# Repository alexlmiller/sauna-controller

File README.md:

# Local & Smart Sauna Controller

Open-source sauna convenience control built around ESPHome and Home Assistant. Control your sauna from anywhere with no cloud dependencies or crappy apps and for 1/3rd the cost of the normal commercial units.

The project can be built two ways:

- **Build from components**: hand-wire off-the-shelf modules and DIN parts.
- **Build with the carrier PCB**: use the Rev B control board PCB for cleaner
  wiring and integrated low-voltage distribution.

Both current build paths use the same Rev B firmware and pin map. The optional
wall panel uses an Elecrow CrowPanel 2.1" rotary display over a short wired UART
link, with a WiFi/Home Assistant panel target available for desk testing.

## Safety

This project is for **convenience control only**. It is not a primary safety
system and must not replace the sauna heater's listed safety controls.

- Use only properly rated, UL/ETL/listed components where applicable.
- Use a heater that already has its required high-limit and safety systems.
- Have the enclosure, high-voltage wiring, grounding, overcurrent protection,
  conductor sizing, strain relief, and final installation reviewed and installed
  by a qualified electrician.
- Do not rely on ESPHome, Home Assistant, WiFi, the wall panel, or this PCB as
  life-safety equipment.

Read [`docs/SAFETY.md`](docs/SAFETY.md) before building.

## What It Controls

- Heater contactor with a 24 VDC coil
- Two DS18B20 temperature probes: ceiling and bench
- Door reed switch
- Manual-reset high-temp circuit in series with the contactor coil
- Relay feedback contact for welded/failed relay detection
- 24 V RGBW LED strip through four PWM MOSFET channels
- Optional wall panel over direct 3.3 V UART

## User Interface

The controller exposes its entities through Home Assistant and can also be used
from a phone dashboard or the optional wall panel.

### Home Assistant Device Page

### Phone Dashboard

## Build Paths

### Option 1: Build From Components

Use an ESP32 DevKitC, MOSFET driver modules, opto input modules, DIN power
supplies, fusing/protection, and terminal blocks. This is best for prototyping
or a one-off hand-wired build.

Start here: [`docs/BUILD-FROM-COMPONENTS.md`](docs/BUILD-FROM-COMPONENTS.md)

### Option 2: Build With the Carrier PCB

Use the Rev B control board carrier PCB. This is the preferred path for new
installs because it reduces point-to-point wiring and integrates the ESP32
carrier, output drivers, opto inputs, PTC protection, 24 V distribution, 5 V
conversion, and field terminals.

Start here: [`docs/BUILD-WITH-CARRIER-PCB.md`](docs/BUILD-WITH-CARRIER-PCB.md)

The design philosophy and current hardware rationale are summarized in
[`docs/DESIGN.md`](docs/DESIGN.md).

## Firmware

Current build targets:

```bash
# Control board
esphome run firmware/control-board/rev-b.yaml

# Normal wired wall panel
esphome run firmware/wall-panel/wired.yaml

# WiFi/Home Assistant wall panel for desk testing
esphome run firmware/wall-panel/wifi.yaml
```

See [`docs/FIRMWARE.md`](docs/FIRMWARE.md) for secrets setup, target layout,
and the legacy Rev A note.

## Wall Panel

The wall panel is optional. The normal installation uses direct 3.3 V UART over
a short Cat5e run and gets 5 V power from the control board. The control board
remains the source of truth for temperature, faults, heat mode, and lighting.

See [`docs/WALL-PANEL.md`](docs/WALL-PANEL.md).

## More Detail

- [`docs/DESIGN.md`](docs/DESIGN.md): design choices and source-of-truth paths.
- [`docs/SAFETY.md`](docs/SAFETY.md): safety boundaries and installation notes.
- [`docs/FIRMWARE.md`](docs/FIRMWARE.md): ESPHome targets and package layout.
- [`docs/WALL-PANEL.md`](docs/WALL-PANEL.md): optional panel behavior and wiring.
- [`pcb/rev-b/README.md`](pcb/rev-b/README.md): KiCad, fabrication, assembly,
  and board verification details.

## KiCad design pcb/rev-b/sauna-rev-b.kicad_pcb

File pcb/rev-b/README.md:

# Rev B Control Board PCB

Complete KiCad design for the Rev B sauna control board. The board carries an
ESP32 DevKitC V4, switches the low-voltage outputs, senses the low-voltage
inputs, distributes 24 V/5 V, and terminates the field wiring cleanly.

This board is part of a **convenience-control** project only. It does not
replace the heater's listed safety systems, required high-limit controls,
proper overcurrent protection, grounding, or code-compliant high-voltage
installation. Use UL/ETL/listed components where applicable and have the final
enclosure and wiring reviewed and installed by a qualified electrician.

For installation-level instructions, start with
[`../../docs/BUILD-WITH-CARRIER-PCB.md`](../../docs/BUILD-WITH-CARRIER-PCB.md).
For design rationale, see [`../../docs/DESIGN.md`](../../docs/DESIGN.md).

## Board Summary

- 120.76 x 88 mm, 2-layer, 1 oz outer copper, 5 mm corner radius, 4x M3 corner
  holes.
- ESP32 DevKitC V4 socket, using ESP32-WROOM-32E or ESP32-WROOM-32D only. Do
  not use WROVER DevKitC variants because Rev B uses GPIO16/GPIO17.
- 24 V input distribution, 24 V to 5 V conversion, and resettable PTC branch
  protection.
- Low-side MOSFET outputs for relay coil, RGBW LEDs, and optional AUX output
  hardware.
- Opto-isolated relay-feedback and high-temp status inputs.
- Separate DS18B20 buses for bench and ceiling sensors.
- Direct 3.3 V UART wall-panel connector with 5 V panel power.

## Connector Layout

The placement follows the cabinet wiring:

| Edge | Connectors | Reason |
|---|---|---|
| Top | `J_PWR`, `J_AUX_OUT` | 24 V PSU is above the board; AUX output can route with top-side low-voltage wiring |
| Left | `J_LED` | LED branch is the highest current low-voltage path, kept short |
| Bottom | `J_PANEL`, `J_DOOR`, `J_BENCH`, `J_CEILING`, `J_SRL250` | Sauna-room and panel wiring enters along the lower side |
| Right | `J_COIL`, `J_RELAY_FB` | Contactor sits to the right, so coil and monitor wiring stay short |

## Key Electrical Choices

- The contactor coil is low-side switched on the board, but heater power stays
  on the external contactor.
- The manual-reset high-temp loop is in series with the contactor coil and is
  also sensed through an opto input.
- Relay feedback uses the contactor auxiliary contact through an opto input.
- RGBW LED outputs are low-side switched and include gate-sensed activity LEDs.
- The optional AUX output is exposed by Rev B firmware as `AUX Output`.
- The on-board FAULT LED follows the firmware's latched fault state.
- The 5 V rail uses a K7805-2000R3 SIP-3 buck converter.
- The board uses a B.Cu ground plane and net classes defined in
  [`tools/design.py`](tools/design.py).

## Files

| File | Purpose |
|---|---|
| `sauna-rev-b.kicad_pro` | KiCad project and design rules |
| `sauna-rev-b.kicad_sch` | Generated schematic |
| `sauna-rev-b.kicad_pcb` | Hand-routed board generated from source plus captured routing |
| `tools/design.py` | Source of truth for nets, parts, pin mapping, and placement |
| `tools/routing.py` | Captured KiCad routing |
| `tools/footprints.py` | Local footprint geometry |
| `tools/generate_schematic.py` | Regenerates the schematic |
| `tools/generate_board.py` | Regenerates the PCB from design data and routing |
| `tools/import_routing.py` | Captures hand-routed traces from KiCad |
| `tools/generate_bom.py` | Regenerates assembly BOM |
| `tools/export_fabrication.py` | Regenerates BOM, CPL, Gerbers, drills, and upload zip |
| `tools/_repro_check.py` | Verifies generated board content matches the checked-in PCB |
| `tools/check_board.py` | Checks clearances and connectivity |
| `fabrication/` | Current fabrication and assembly outputs |

## Edit Workflow

Routing and final placement are edited in KiCad, then captured back into the
generator inputs. After KiCad edits:

```bash
cd pcb/rev-b
python3 -m venv .venv && .venv/bin/pip install kiutils numpy
.venv/bin/python tools/import_routing.py
.venv/bin/python tools/_design_diff.py
.venv/bin/python tools/_silk_diff.py
.venv/bin/python tools/_repro_check.py
.venv/bin/python tools/generate_board.py
.venv/bin/python tools/check_board.py
```

Before ordering, also run KiCad ERC/DRC locally with zones filled.

## Assembly Notes

The Rev B board is intended to be supplier-assembled, including terminal blocks,
ESP sockets, electrolytics, K7805 buck, and resettable PTCs. The generated
assembly files are in [`fabrication/`](fabrication/).

Current notable JLC/LCSC selections include:

- AOD4184A MOSFETs: `C99124`
- SS54 Schottky diodes: `C22452`
- SMBJ30CA TVS diodes: `C5331115`
- F1 LED PTC: `C719172`
- F4 AUX PTC: `C139284`

Verify stock, polarity, substitutions, and physical fit before ordering. Print
the board 1:1 and test-fit the DevKitC, terminal blocks, PTCs, K7805, SOP-4
opto parts, and electrolytic capacitors.

## Verification

Machine checks in this repo cover courtyard overlaps, board boundary, antenna
keepout, per-net-class copper/edge clearance, and single-island connectivity.

Before installing a fabricated board:

1. Inspect polarity, soldering, terminal labels, and ESP32 orientation.
2. Confirm 24 V input, 5 V output, and 3.3 V ESP rail with no field loads.
3. Bench-test relay-feedback and high-temp opto channels with 24 V.
4. Test each LED channel with a current-limited load.
5. Test contactor coil control before energizing the heater circuit.

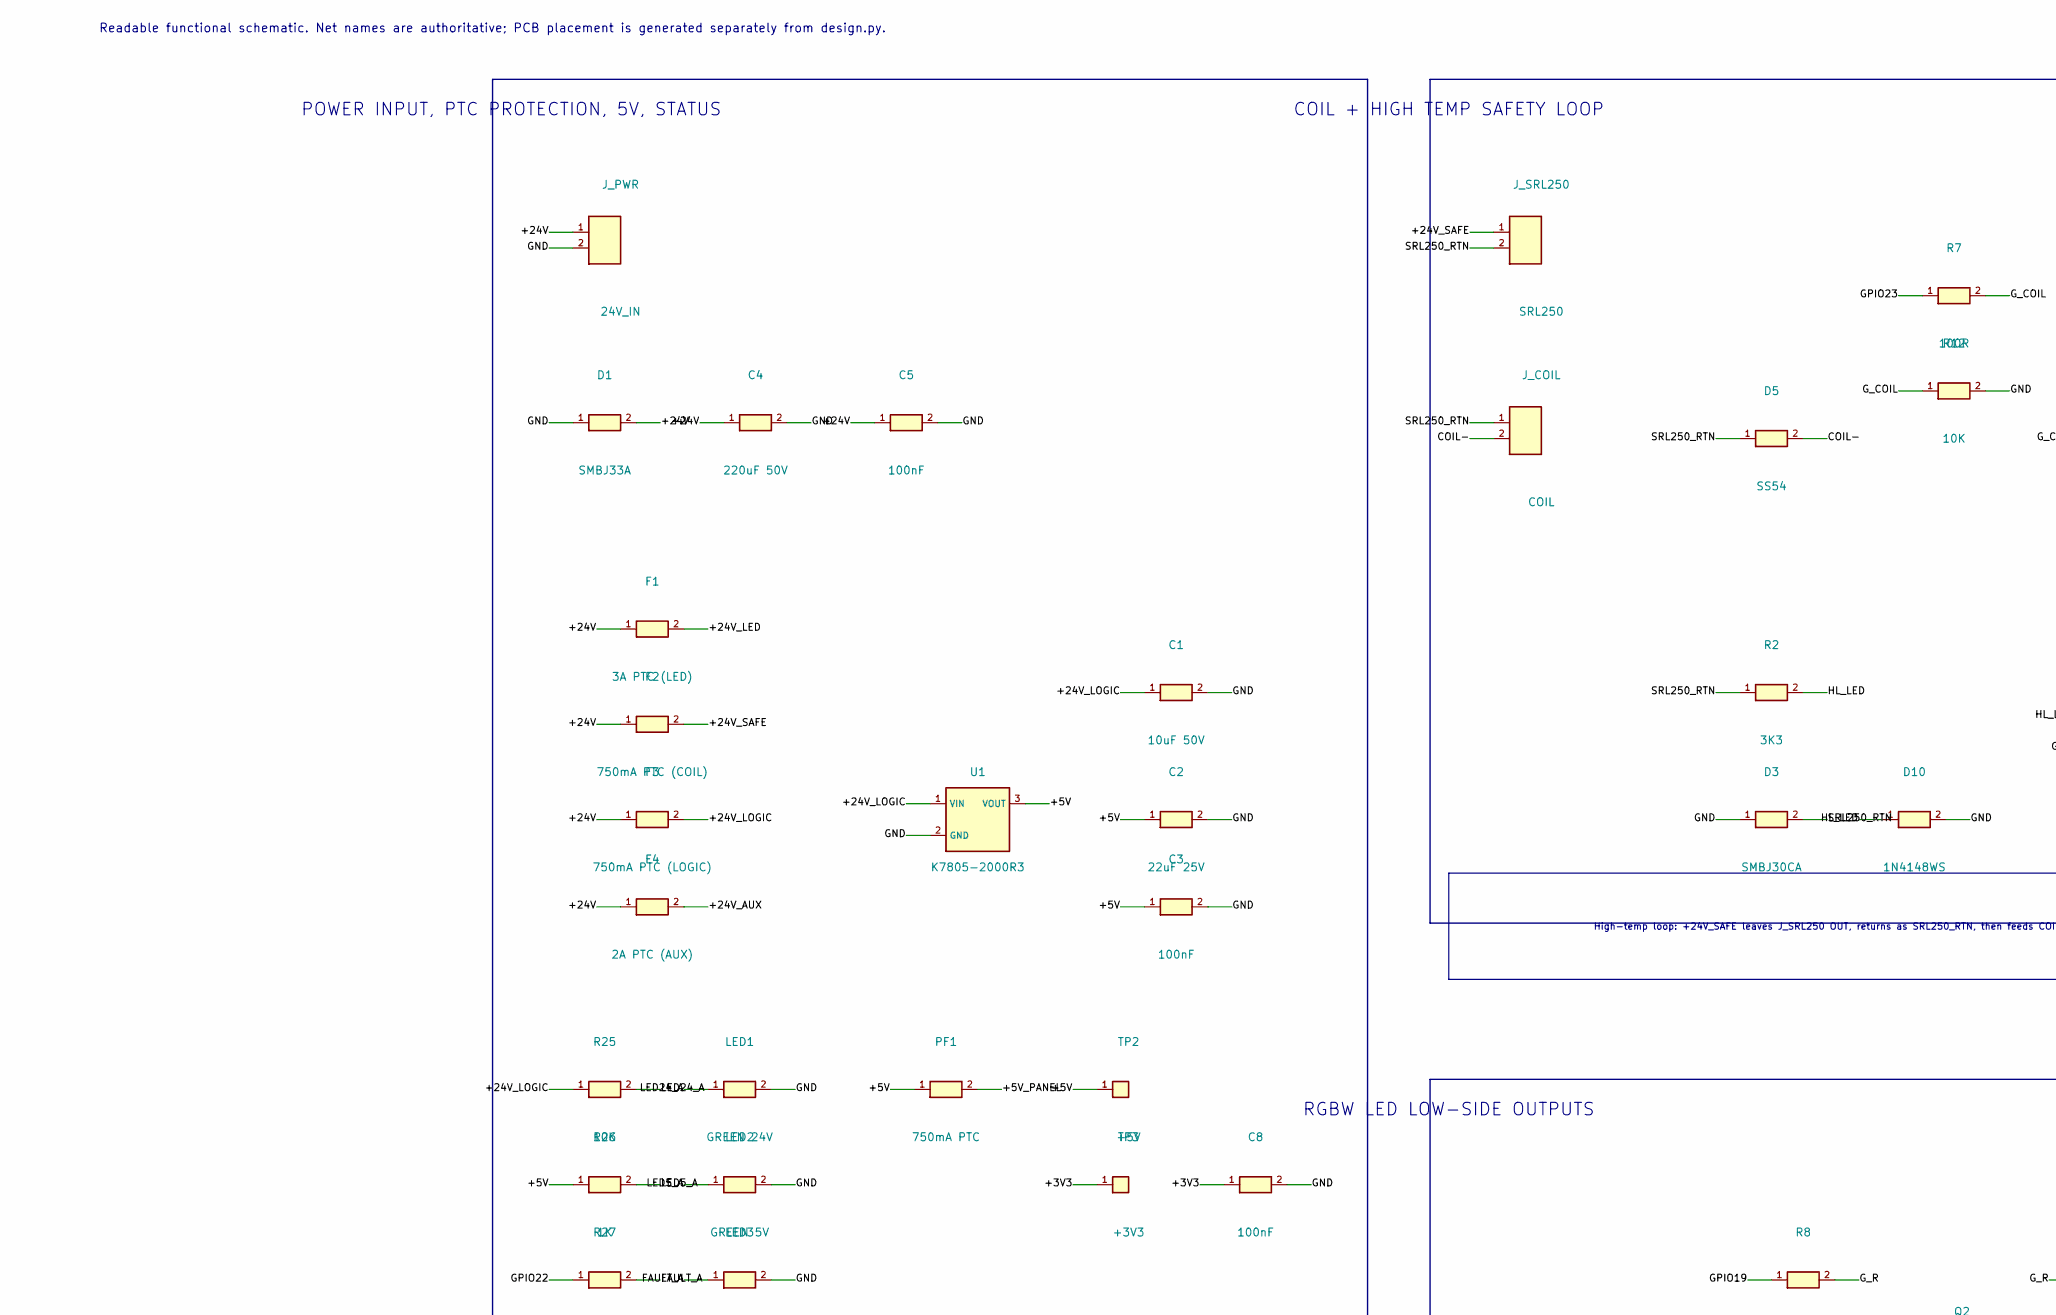
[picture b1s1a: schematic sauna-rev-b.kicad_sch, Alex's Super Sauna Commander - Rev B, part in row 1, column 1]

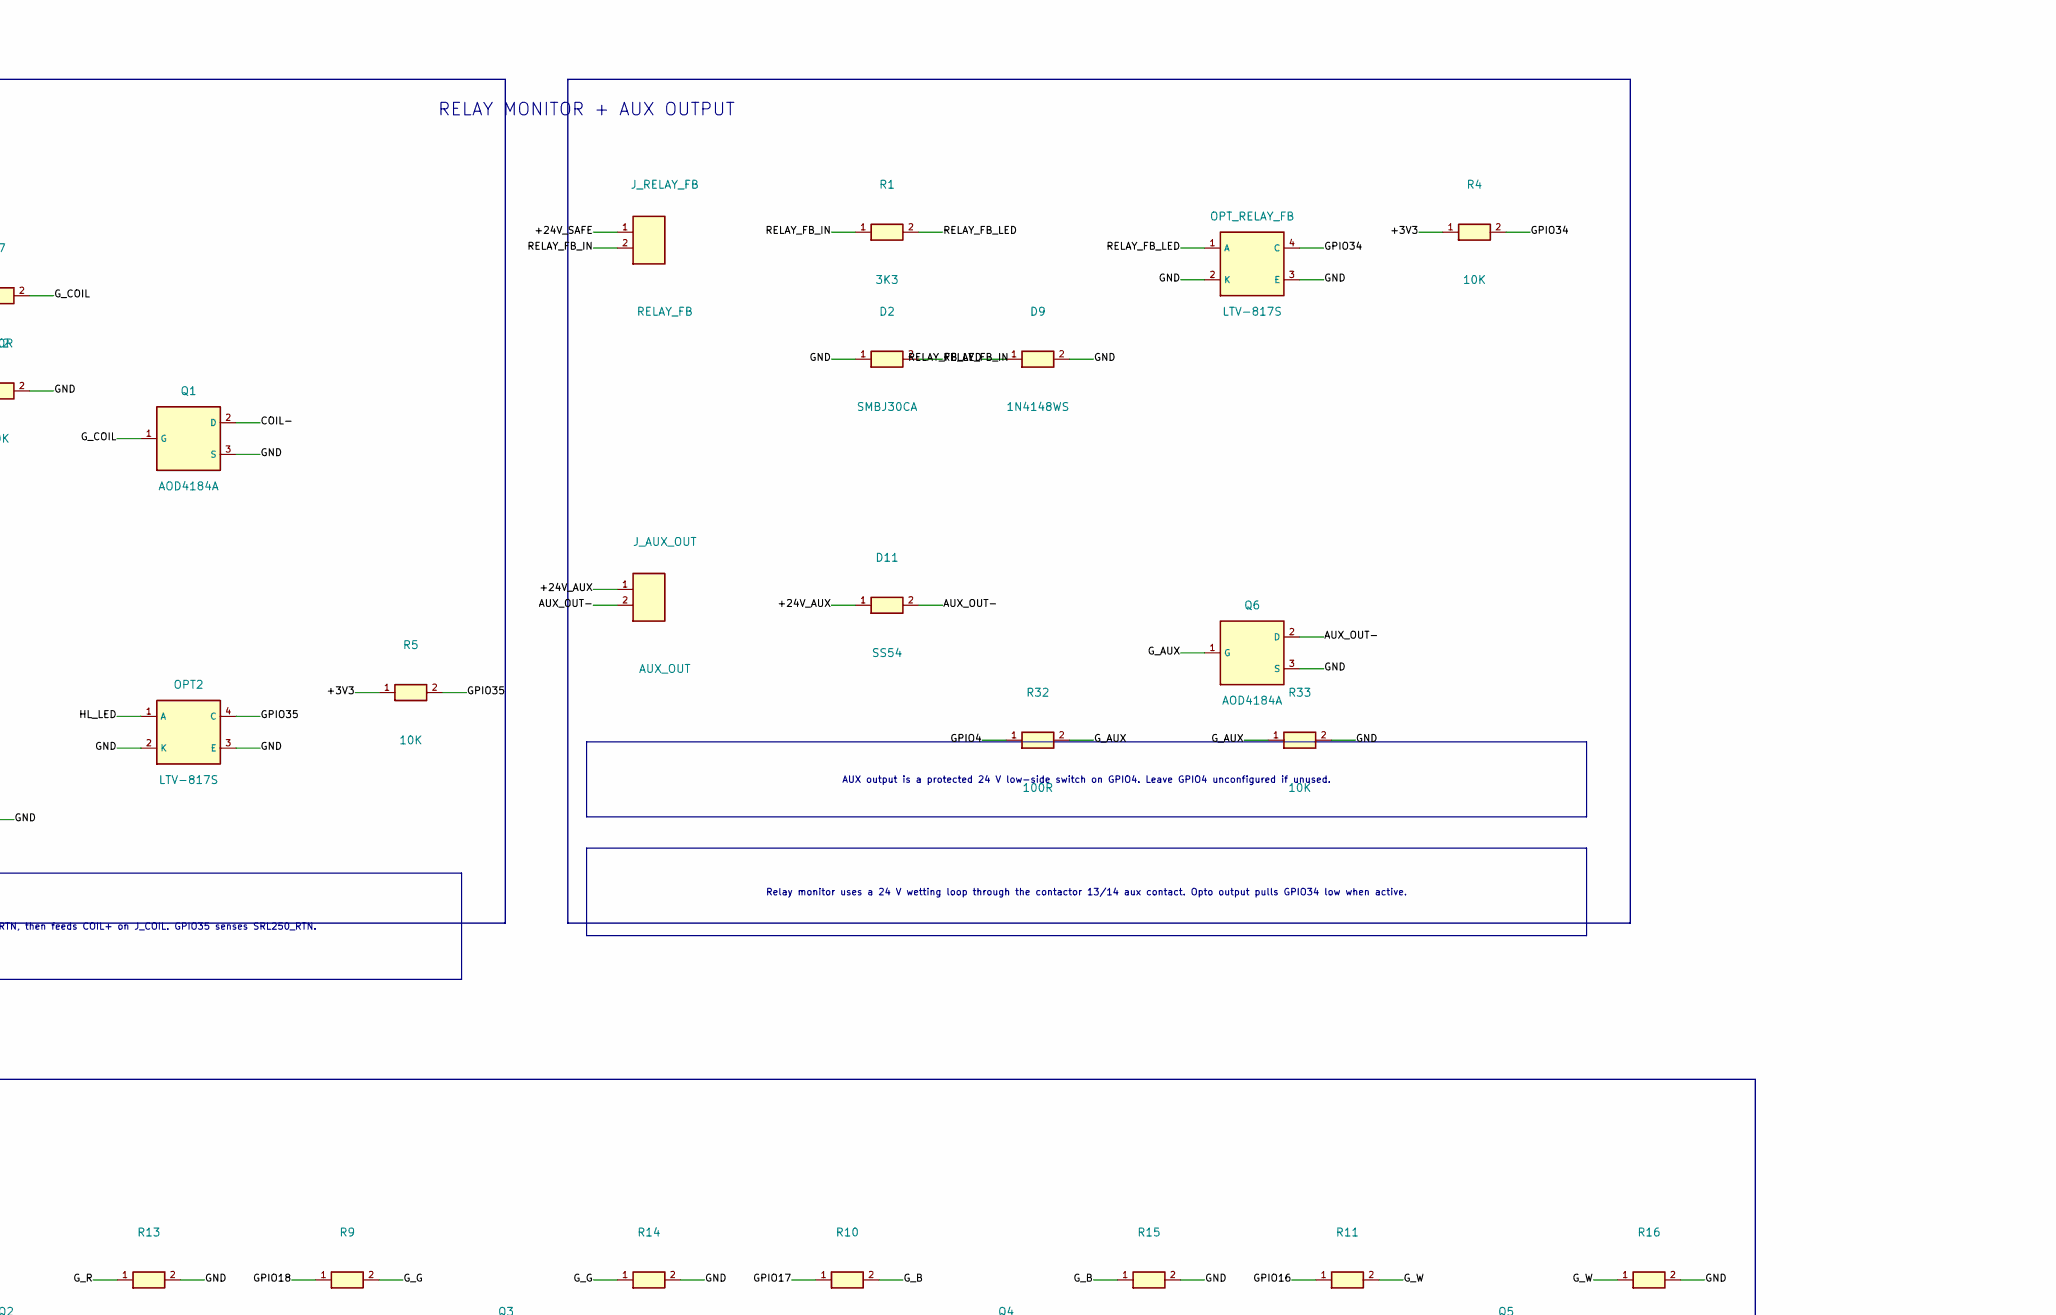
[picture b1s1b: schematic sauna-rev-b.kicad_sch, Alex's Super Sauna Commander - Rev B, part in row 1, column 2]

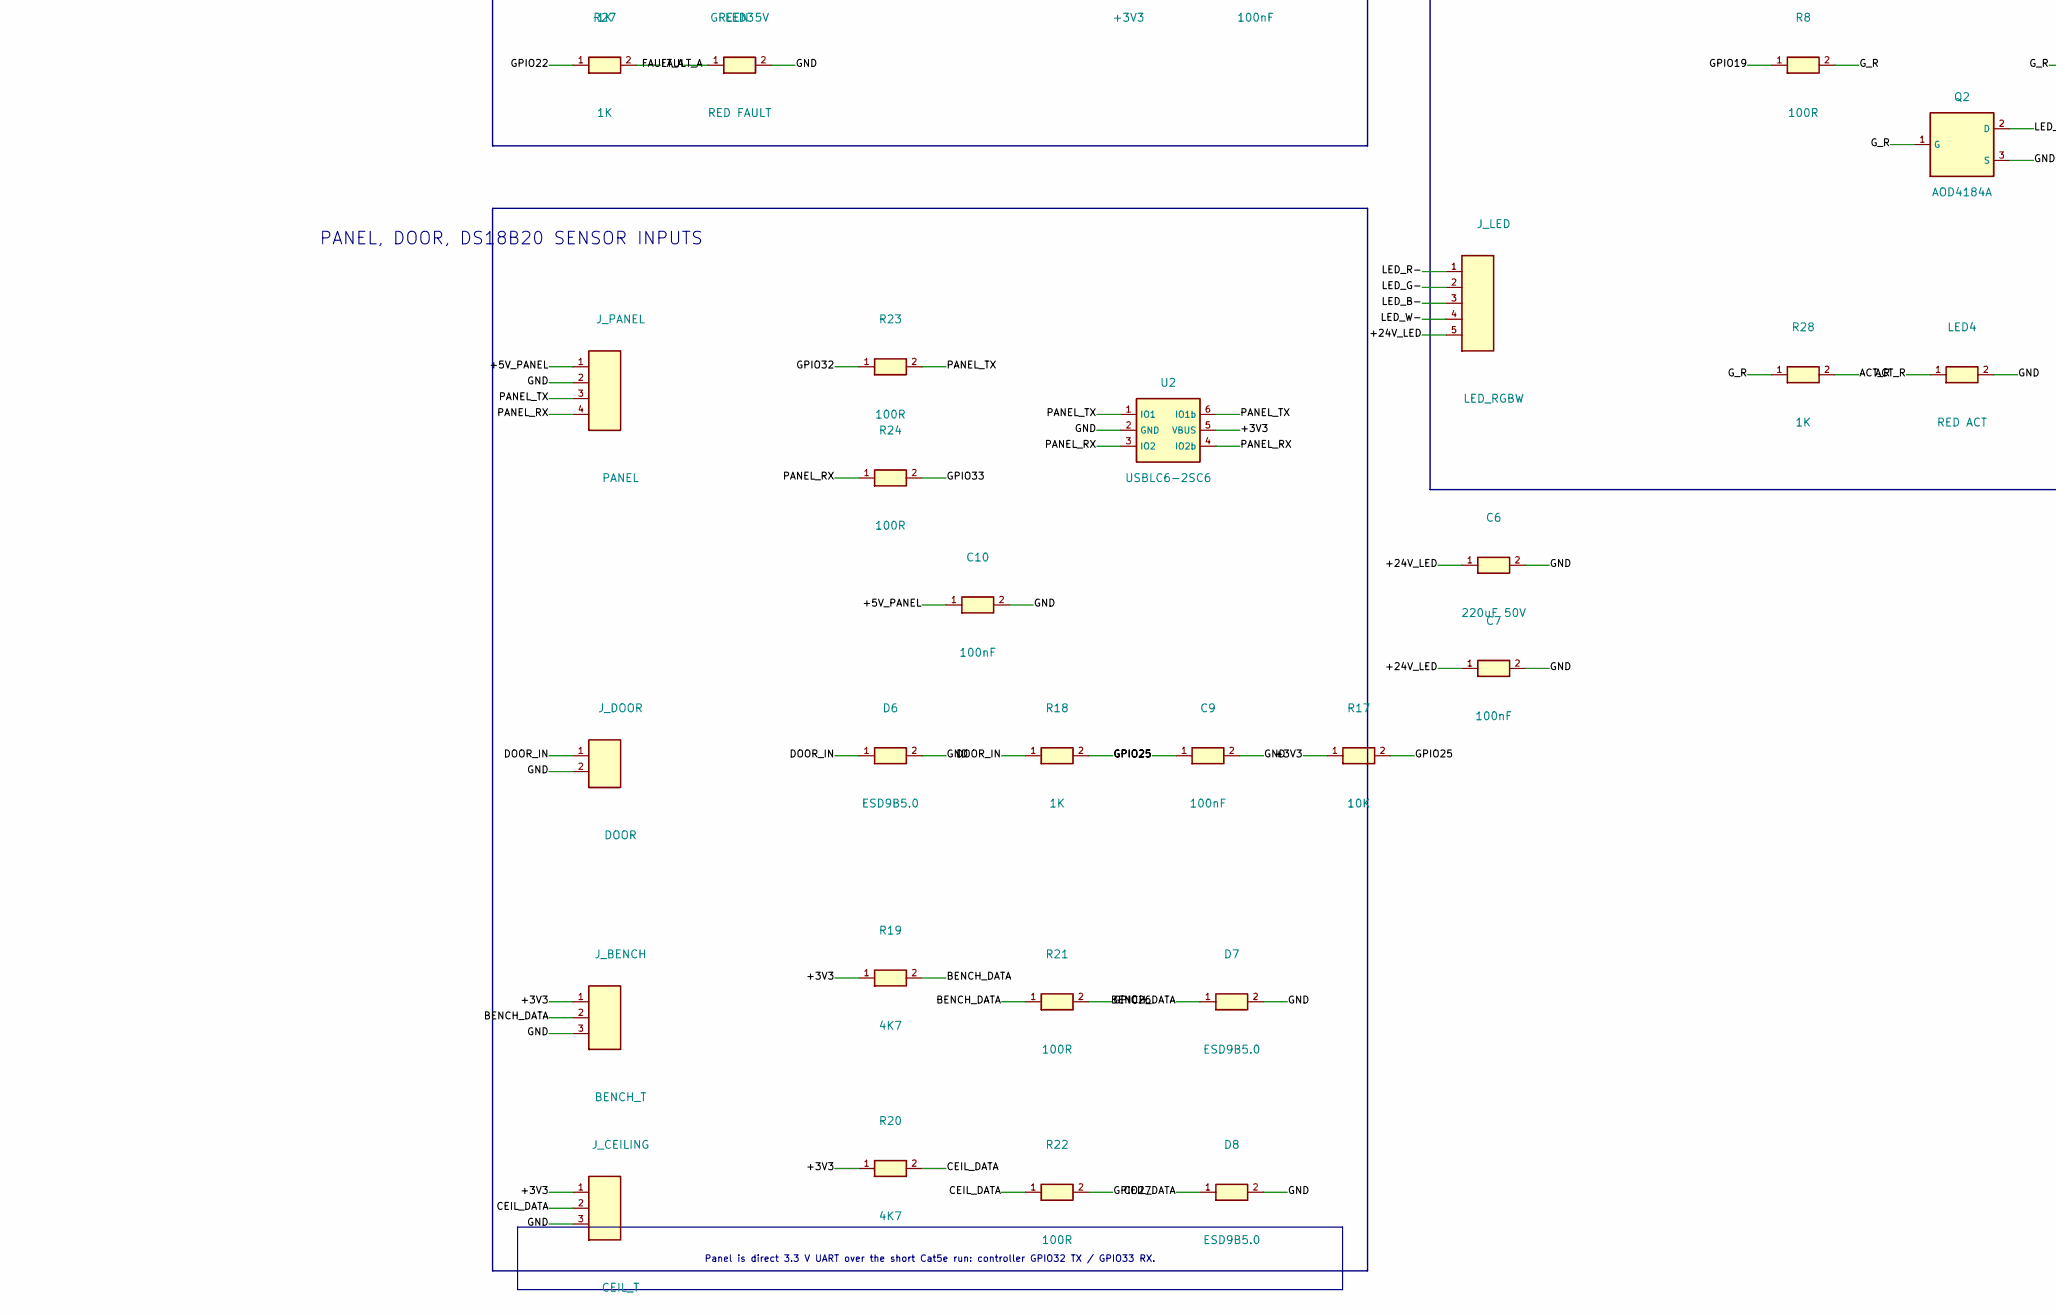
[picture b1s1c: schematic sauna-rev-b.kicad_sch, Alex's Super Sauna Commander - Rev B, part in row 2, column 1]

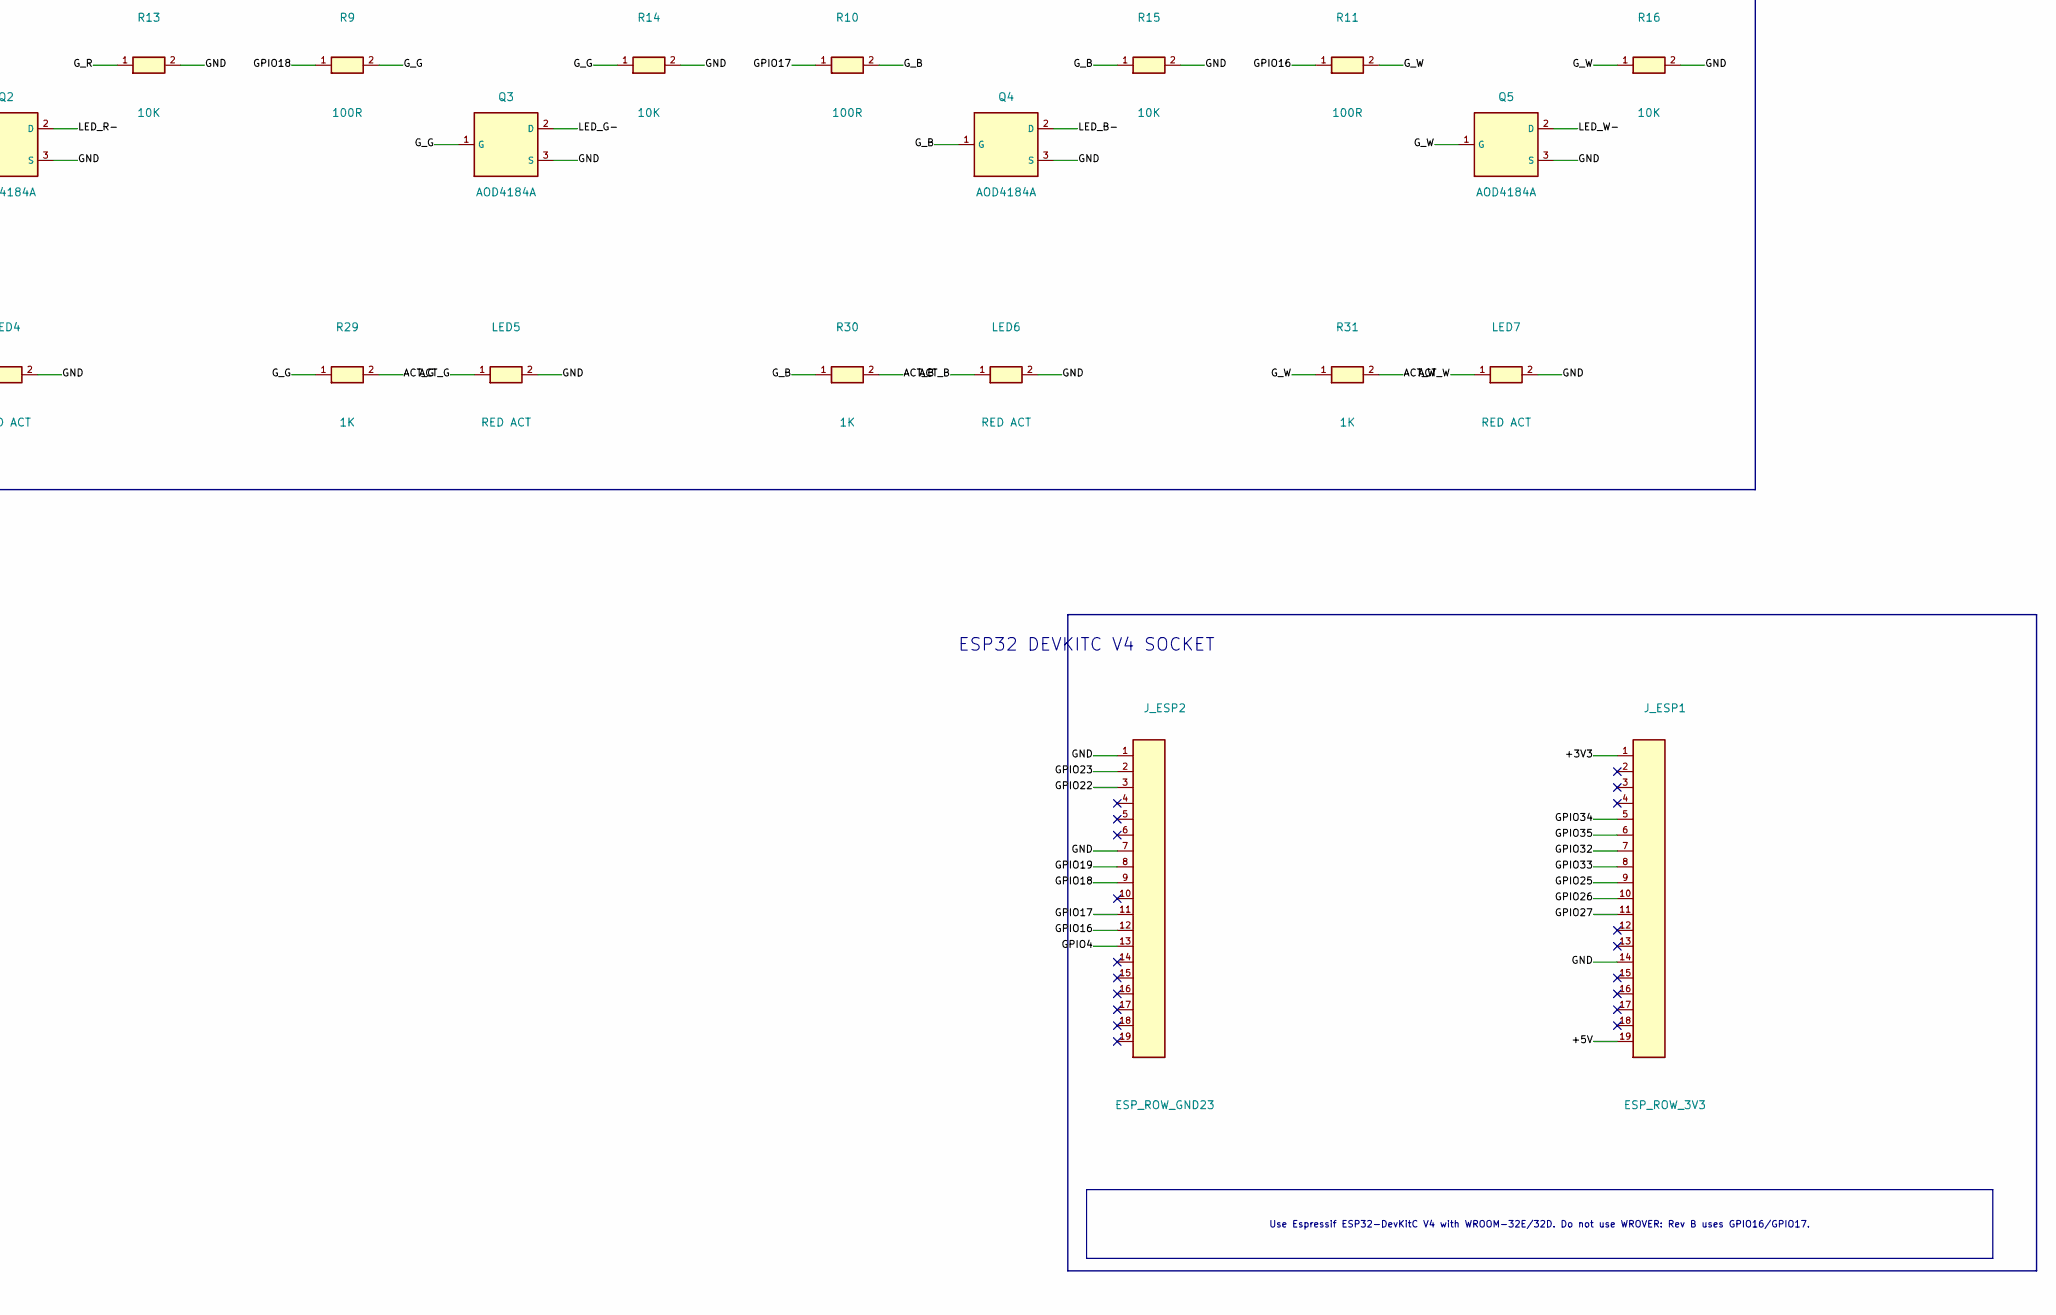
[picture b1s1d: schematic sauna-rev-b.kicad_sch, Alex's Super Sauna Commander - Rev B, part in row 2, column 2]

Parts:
C1: 10uF 50V; C_1210; LCSC C138687
C2: 22uF 25V; C_1210; LCSC C52306
C3, C5, C7, C8, C9, C10: 100nF; C_0805; LCSC C49678
C4, C6: 220uF 50V; CP_D8_P3.5; LCSC C106658
D1: SMBJ33A; D_SMB; MPN SMBJ33A; LCSC C78419
D2, D3: SMBJ30CA; D_SMB; MPN SMBJ30CA; LCSC C5331115
D5, D11: SS54; D_SMA; MPN SS54; LCSC C22452
D6, D7, D8: ESD9B5.0; D_SOD923; MPN ESD9B5.0ST5G; LCSC C111566
D9, D10: 1N4148WS; D_SOD323; LCSC C2128
F1: 3A PTC (LED); PTC_2920; MPN JLC C719172; LCSC C719172
F2: 750mA PTC (COIL); PTC_1812; MPN Bourns MF-MSMF075/24-2 or equivalent; LCSC C208467
F3: 750mA PTC (LOGIC); PTC_1812; MPN Bourns MF-MSMF075/24-2 or equivalent; LCSC C208467
F4: 2A PTC (AUX); PTC_2920; MPN JLC C139284; LCSC C139284
J_AUX_OUT: AUX_OUT; MKDS_2; MPN Phoenix MKDS 1,5/2-5,08; LCSC C8461
J_BENCH: BENCH_T; MKDS_3; MPN Phoenix MKDS 1,5/3-5,08; LCSC C8438
J_CEILING: CEIL_T; MKDS_3; MPN Phoenix MKDS 1,5/3-5,08; LCSC C8438
J_COIL: COIL; MKDS_2; MPN Phoenix MKDS 1,5/2-5,08; LCSC C8461
J_DOOR: DOOR; MKDS_2; MPN Phoenix MKDS 1,5/2-5,08; LCSC C8461
J_ESP1: ESP_ROW_3V3; SOCKET_1x19; MPN PinSocket 1x19 2.54mm; LCSC C319202
J_ESP2: ESP_ROW_GND23; SOCKET_1x19; MPN PinSocket 1x19 2.54mm; LCSC C319202
J_LED: LED_RGBW; MKDS_5; MPN Phoenix MKDS 1,5/5-5,08; LCSC C8433
J_PANEL: PANEL; MKDS_4; MPN Phoenix MKDS 1,5/4-5,08; LCSC C8429
J_PWR: 24V_IN; MKDS_2; MPN Phoenix MKDS 1,5/2-5,08; LCSC C8461
J_RELAY_FB: RELAY_FB; MKDS_2; MPN Phoenix MKDS 1,5/2-5,08; LCSC C8461
J_SRL250: SRL250; MKDS_2; MPN Phoenix MKDS 1,5/2-5,08; LCSC C8461
LED1: GREEN 24V; LED_0805; LCSC C2297
LED2: GREEN 5V; LED_0805; LCSC C2297
LED3: RED FAULT; LED_0805; LCSC C2295
LED4, LED5, LED6, LED7: RED ACT; LED_0805; MPN red 0805; LCSC C2295
OPT2: LTV-817S; SOP4_OPTO; MPN LTV-817S; LCSC C109227
OPT_RELAY_FB: LTV-817S; SOP4_OPTO; MPN LTV-817S; LCSC C109227
PF1: 750mA PTC; R_1812; MPN MF-MSMF075/24X; LCSC C208467
Q1, Q2, Q3, Q4, Q5, Q6: AOD4184A; TO252; MPN AOD4184A; LCSC C99124
R1, R2: 3K3; R_1206; LCSC C104771
R4, R5, R12, R13, R14, R15, R16, R17, R25, R33: 10K; R_0805; LCSC C17414
R7, R8, R9, R10, R11, R21, R22, R23, R24, R32: 100R; R_0805; LCSC C17408
R18, R26, R27, R28, R29, R30, R31: 1K; R_0805; LCSC C17513
R19, R20: 4K7; R_0805; LCSC C17673
TP2: +5V; TESTPOINT
TP3: +3V3; TESTPOINT
U1: K7805-2000R3; SIP3_REG; MPN K7805-2000R3; LCSC C18212380
U2: USBLC6-2SC6; SOT23_6; MPN USBLC6-2SC6; LCSC C7519

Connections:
+3V3: C8.1, J_BENCH.1, J_CEILING.1, J_ESP1.1, R4.1, R5.1, R17.1, R19.1, R20.1, TP3.1, U2.5 (VBUS)
+5V: C2.1, C3.1, J_ESP1.19, PF1.1, R26.1, TP2.1, U1.3 (VOUT)
+5V_PANEL: C10.1, J_PANEL.1, PF1.2
+24V: C4.1, C5.1, D1.2, F1.1, F2.1, F3.1, F4.1, J_PWR.1
+24V_AUX: D11.1, F4.2, J_AUX_OUT.1
+24V_LED: C6.1, C7.1, F1.2, J_LED.5
+24V_LOGIC: C1.1, F3.2, R25.1, U1.1 (VIN)
+24V_SAFE: F2.2, J_RELAY_FB.1, J_SRL250.1
ACT_B: LED6.1, R30.2
ACT_G: LED5.1, R29.2
ACT_R: LED4.1, R28.2
ACT_W: LED7.1, R31.2
AUX_OUT-: D11.2, J_AUX_OUT.2, Q6.2 (D)
BENCH_DATA: D7.1, J_BENCH.2, R19.2, R21.1
CEIL_DATA: D8.1, J_CEILING.2, R20.2, R22.1
COIL-: D5.2, J_COIL.2, Q1.2 (D)
DOOR_IN: D6.1, J_DOOR.1, R18.1
FAULT_A: LED3.1, R27.2
GND: C1.2, C2.2, C3.2, C4.2, C5.2, C6.2, C7.2, C8.2, C9.2, C10.2, D1.1, D2.1, D3.1, D6.2, D7.2, D8.2, D9.2, D10.2, J_BENCH.3, J_CEILING.3, J_DOOR.2, J_ESP1.14, J_ESP2.1, J_ESP2.7, J_PANEL.2, J_PWR.2, LED1.2, LED2.2, LED3.2, LED4.2, LED5.2, LED6.2, LED7.2, OPT2.2 (K), OPT2.3 (E), OPT_RELAY_FB.2 (K), OPT_RELAY_FB.3 (E), Q1.3 (S), Q2.3 (S), Q3.3 (S), Q4.3 (S), Q5.3 (S), Q6.3 (S), R12.2, R13.2, R14.2, R15.2, R16.2, R33.2, U1.2 (GND), U2.2 (GND)
GPIO4: J_ESP2.13, R32.1
GPIO16: J_ESP2.12, R11.1
GPIO17: J_ESP2.11, R10.1
GPIO18: J_ESP2.9, R9.1
GPIO19: J_ESP2.8, R8.1
GPIO22: J_ESP2.3, R27.1
GPIO23: J_ESP2.2, R7.1
GPIO25: C9.1, J_ESP1.9, R17.2, R18.2
GPIO26: J_ESP1.10, R21.2
GPIO27: J_ESP1.11, R22.2
GPIO32: J_ESP1.7, R23.1
GPIO33: J_ESP1.8, R24.2
GPIO34: J_ESP1.5, OPT_RELAY_FB.4 (C), R4.2
GPIO35: J_ESP1.6, OPT2.4 (C), R5.2
G_AUX: Q6.1 (G), R32.2, R33.1
G_B: Q4.1 (G), R10.2, R15.1, R30.1
G_COIL: Q1.1 (G), R7.2, R12.1
G_G: Q3.1 (G), R9.2, R14.1, R29.1
G_R: Q2.1 (G), R8.2, R13.1, R28.1
G_W: Q5.1 (G), R11.2, R16.1, R31.1
HL_LED: D10.1, OPT2.1 (A), R2.2
LED5_A: LED2.1, R26.2
LED24_A: LED1.1, R25.2
LED_B-: J_LED.3, Q4.2 (D)
LED_G-: J_LED.2, Q3.2 (D)
LED_R-: J_LED.1, Q2.2 (D)
LED_W-: J_LED.4, Q5.2 (D)
PANEL_RX: J_PANEL.4, R24.1, U2.3 (IO2), U2.4 (IO2b)
PANEL_TX: J_PANEL.3, R23.2, U2.1 (IO1), U2.6 (IO1b)
RELAY_FB_IN: D2.2, J_RELAY_FB.2, R1.1
RELAY_FB_LED: D9.1, OPT_RELAY_FB.1 (A), R1.2
SRL250_RTN: D3.2, D5.1, J_COIL.1, J_SRL250.2, R2.1

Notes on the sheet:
High-temp loop: +24V_SAFE leaves J_SRL250 OUT, returns as SRL250_RTN, then feeds COIL+ on J_COIL. GPIO35 senses SRL250_RTN.
Relay monitor uses a 24 V wetting loop through the contactor 13/14 aux contact. Opto output pulls GPIO34 low when active.
AUX output is a protected 24 V low-side switch on GPIO4. Leave GPIO4 unconfigured if unused.
Use Espressif ESP32-DevKitC V4 with WROOM-32E/32D. Do not use WROVER: Rev B uses GPIO16/GPIO17.
Panel is direct 3.3 V UART over the short Cat5e run: controller GPIO32 TX / GPIO33 RX.
POWER INPUT, PTC PROTECTION, 5V, STATUS
COIL + HIGH TEMP SAFETY LOOP
RELAY MONITOR + AUX OUTPUT
RGBW LED LOW-SIDE OUTPUTS
PANEL, DOOR, DS18B20 SENSOR INPUTS
ESP32 DEVKITC V4 SOCKET
Readable functional schematic. Net names are authoritative; PCB placement is generated separately from design.py.

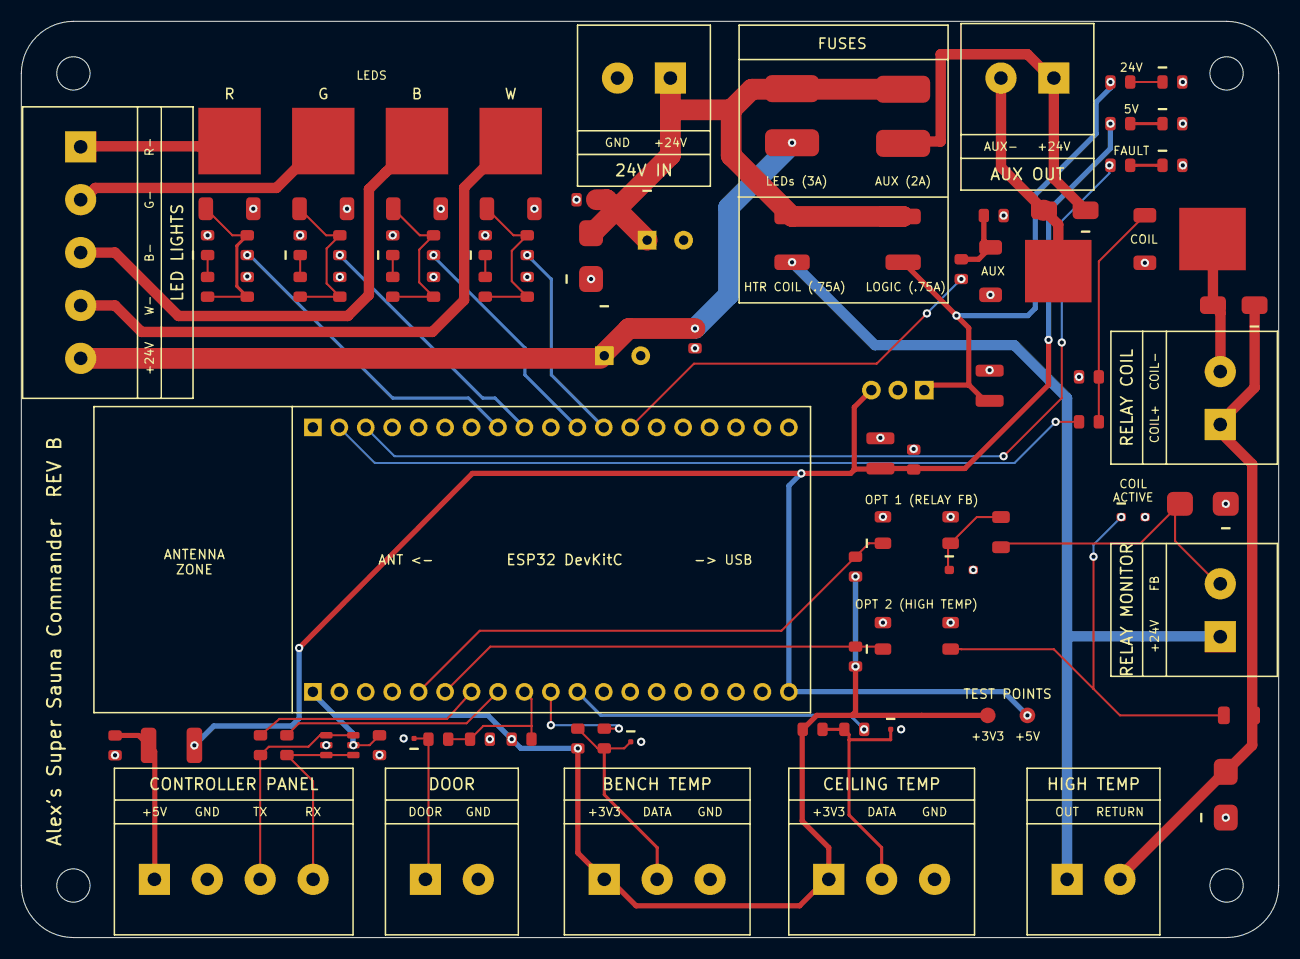
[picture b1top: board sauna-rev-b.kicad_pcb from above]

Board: 2 copper layers, 120.8 x 88.0 mm, 91 parts (0 on the bottom side), 51 nets.

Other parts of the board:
H1, H2, H3, H4: M3; MountingHole_M3_NPTH

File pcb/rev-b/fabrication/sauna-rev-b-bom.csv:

Comment,Designator,Footprint,JLCPCB Part #
ESP_ROW_3V3,J_ESP1,1x19 2.54mm female header,C319202
ESP_ROW_GND23,J_ESP2,1x19 2.54mm female header,C319202
100nF,"C3,C5,C7,C8,C9,C10",C0805,C49678
10uF 50V,C1,C1210,C138687
22uF 25V,C2,C1210,C52306
GREEN 24V,LED1,LED0805,C2297
GREEN 5V,LED2,LED0805,C2297
RED ACT,"LED4,LED5,LED6,LED7",LED0805,C2295
RED FAULT,LED3,LED0805,C2295
750mA PTC (COIL),F2,PTC1812,C208467
750mA PTC (LOGIC),F3,PTC1812,C208467
2A PTC (AUX),F4,PTC2920,C139284
3A PTC (LED),F1,PTC2920,C719172
100R,"R7,R8,R9,R10,R11,R21,R22,R23,R24,R32",R0805,C17408
10K,"R4,R5,R12,R13,R14,R15,R16,R17,R25,R33",R0805,C17414
1K,"R18,R26,R27,R28,R29,R30,R31",R0805,C17513
4K7,"R19,R20",R0805,C17673
3K3,"R1,R2",R1206,C104771
750mA PTC,PF1,R1812,C208467
220uF 50V,"C4,C6",Radial D8.0mm P3.50mm,C106658
K7805-2000R3,U1,"SIP-3,2.54mm",C18212380
SS54,"D5,D11","SMA,DO-214AC",C22452
SMBJ30CA,"D2,D3","SMB,DO-214AA",C5331115
SMBJ33A,D1,"SMB,DO-214AA",C78419
1N4148WS,"D9,D10",SOD-323,C2128
ESD9B5.0,"D6,D7,D8",SOD-923,C111566
LTV-817S,"OPT_RELAY_FB,OPT2",SOP-4,C109227
USBLC6-2SC6,U2,SOT-23-6,C7519
AOD4184A,"Q1,Q2,Q3,Q4,Q5,Q6","TO-252-2,DPAK",C99124
24V_IN,J_PWR,Terminal 5.08mm 2P,C8461
AUX_OUT,J_AUX_OUT,Terminal 5.08mm 2P,C8461
COIL,J_COIL,Terminal 5.08mm 2P,C8461
DOOR,J_DOOR,Terminal 5.08mm 2P,C8461
RELAY_FB,J_RELAY_FB,Terminal 5.08mm 2P,C8461
SRL250,J_SRL250,Terminal 5.08mm 2P,C8461
BENCH_T,J_BENCH,Terminal 5.08mm 3P,C8438
CEIL_T,J_CEILING,Terminal 5.08mm 3P,C8438
PANEL,J_PANEL,Terminal 5.08mm 4P,C8429
LED_RGBW,J_LED,Terminal 5.08mm 5P,C8433
